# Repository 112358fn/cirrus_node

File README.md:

# Nodes of Sensor Cirrus
On Sensor Cirrus nodes are basically a microprocessor that has attached sensors and a XBee End-Device. This node will connect though the XBee with its coordinator(see [cirrus_coordinator](https://github.com/112358fn/cirrus_coordinator)) to transmit the sensor values and receive the refresh date of those readings.   

## Files
The files are organized in this way

1. Arduino UNO:
  * Firmware: Arduino code for the node and the configuration files of Coordinator and End-Device Xbees(those files has to be uploaded to the XBees through the XCTU software)
  * Shield: A simple shield so SHT17 can be welded and the board XBTS from IT&T can be conected directly. These board was made on Eagle 7.6 Freeware License
  
2. Arduino PRO:
  * Firmware: (Same as Arduino UNO) but this firmware uses a SHT15 sensor so the libraries are diferent.

3. Doc: Various documentation files that can be useful for undertandig or for further development

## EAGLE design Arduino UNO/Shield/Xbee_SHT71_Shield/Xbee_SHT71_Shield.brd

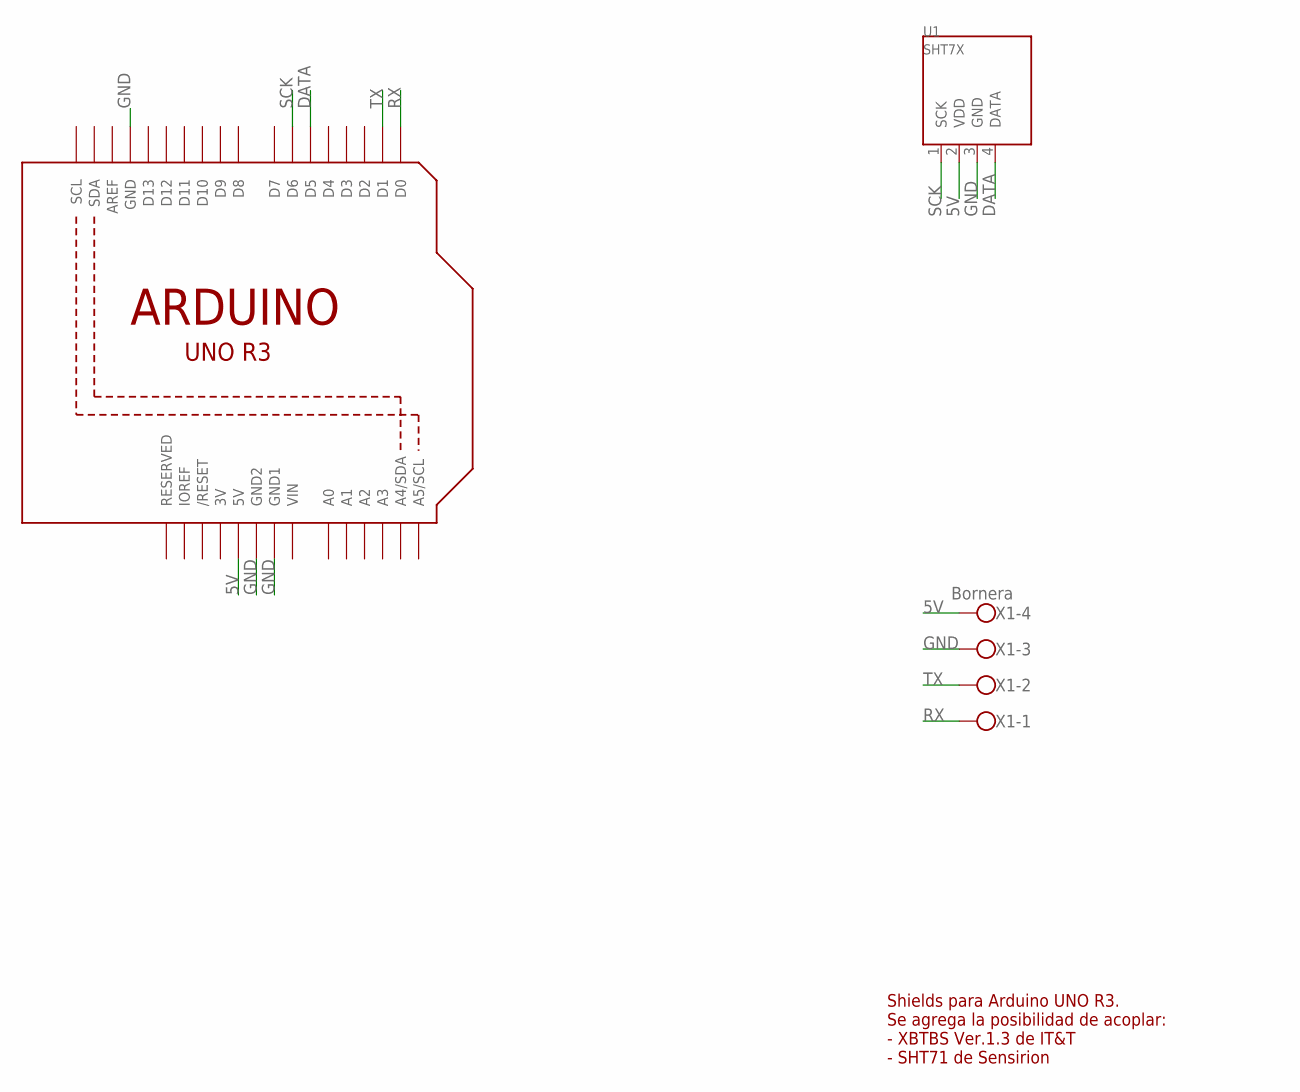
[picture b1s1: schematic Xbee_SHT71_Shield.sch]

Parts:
U1: SHT7X
U2: ARDUINOR3-DIMENSION; ARDUINOR3
X1: Bornera; W237-4

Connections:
3V: U2.3V
5V: U1.2 (VDD), U2.5V, X1.4
DATA: U1.4 (DATA), U2.D5
GND: U1.3 (GND), U2.GND, U2.GND1, U2.GND2, X1.3
RX: U2.D0, X1.1
SCK: U1.1 (SCK), U2.D6
TX: U2.D1, X1.2
VIN: U2.VIN

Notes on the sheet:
Shields para Arduino UNO R3. Se agrega la posibilidad de acoplar: - XBTBS Ver.1.3 de IT&T - SHT71 de Sensirion

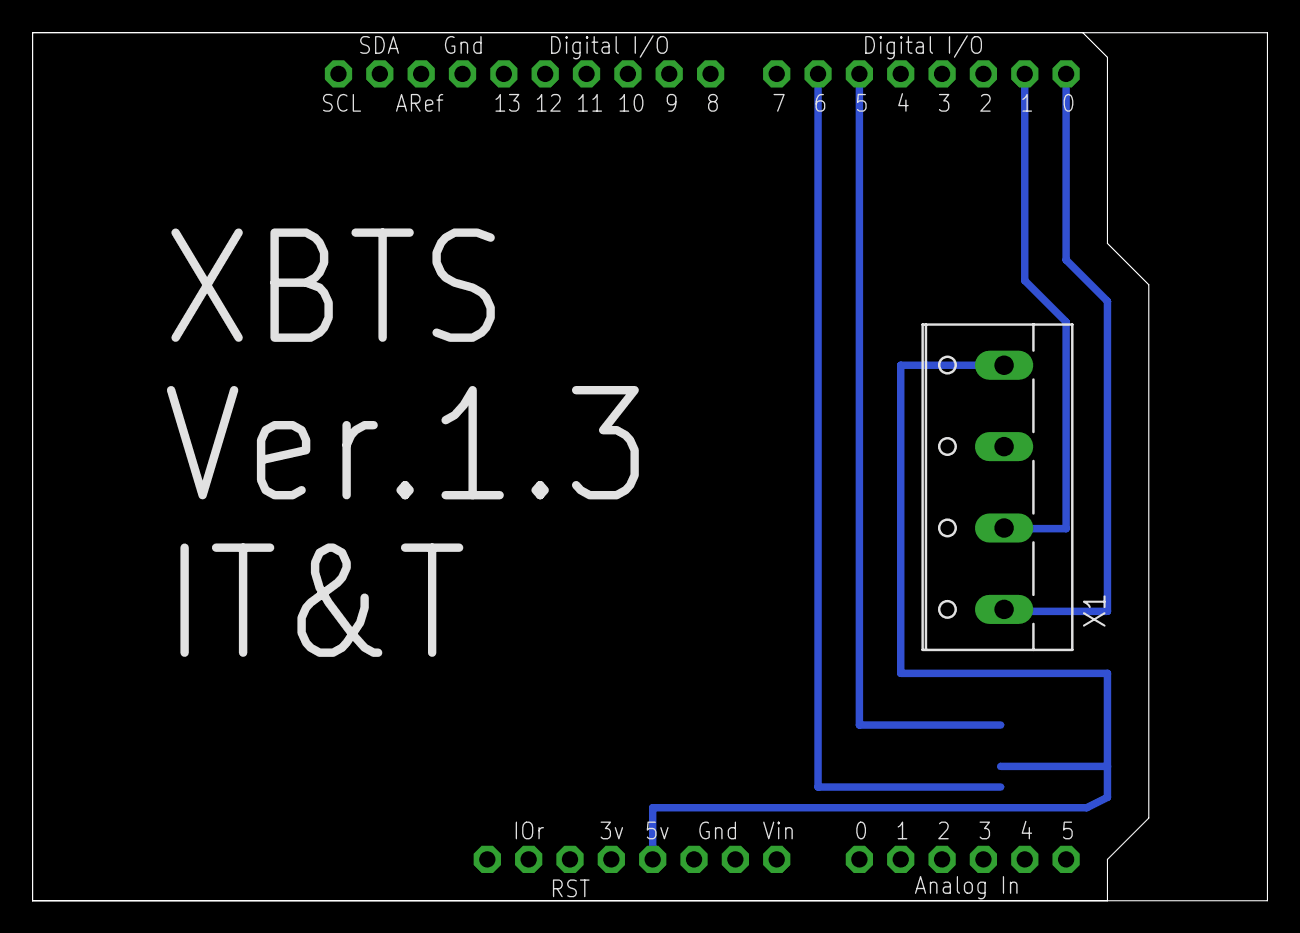
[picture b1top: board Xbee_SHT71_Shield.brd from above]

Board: 2 copper layers, 75.9 x 53.3 mm, 3 parts (1 on the bottom side), 6 nets.

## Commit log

2016-11-07 Added ignore for mac
2016-11-07 Added code for nodes
2016-11-07 Updated Description

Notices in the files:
parts and their libraries:
SparkFun-Sensors: Licensing: Creative Commons ShareAlike 4.0 International - https://creativecommons.org/licenses/by-sa/4.0
